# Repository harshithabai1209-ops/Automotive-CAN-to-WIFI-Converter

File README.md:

🚗 Automotive CAN-to-WiFi Converter(PCB DESIGN)
📌 Overview

This project implements an Automotive CAN (Controller Area Network) to Wi-Fi converter using a microcontroller with integrated Wi-Fi and a custom PCB designed in KiCad.
It allows vehicles’ CAN bus data (speed, RPM, fuel level, sensor data, etc.) to be captured, processed, and transmitted over Wi-Fi to mobile apps.

🚀 Features

Interfaces with standard Automotive CAN bus (OBD-II, ISO 11898)

Converts CAN frames into Wi-Fi packets

Supports protocols: MQTT, HTTP, WebSocket

Designed for low-latency data streaming

Custom KiCad PCB with CAN transceiver + Wi-Fi MCU

Optional SD card logging for offline analysis

Can be used for telematics, diagnostics, and fleet monitoring

🛠️ Hardware Components

Microcontroller (ESP32 / STM32 + ESP8266) → Wi-Fi + processing

CAN Transceiver (MCP2551 / SN65HVD230) → Interface between CAN bus & MCU

OBD-II Connector → Connection to vehicle CAN lines (CAN_H, CAN_L)

Power Supply

12V from car → Buck converter → 5V/3.3V regulated

Automotive-grade regulator (LM2596 / MP1584)

Protection Circuits

TVS Diodes for CAN line protection

Fuse & reverse polarity protection

Optional Modules

SD card (logging)

OLED/LCD (local display)

📐 PCB Design (KiCad)

Designed using KiCad EDA

2-layer PCB optimized for automotive use

Includes CAN transceiver + ESP32 footprint

Proper decoupling capacitors and EMI filters

Ground plane isolation between noisy CAN and Wi-Fi section

Connector footprint for OBD-II interface

Gerber files ready for fabrication

⚙️ Firmware / Software

Developed using Arduino IDE / ESP-IDF / STM32Cube

Features:

Reads CAN frames via CAN transceiver

Publishes data over Wi-Fi (MQTT/HTTP/WebSocket)

Supports real-time monitoring dashboard

Configurable baud rates (125 kbps, 250 kbps, 500 kbps)

🧩 Applications

Vehicle diagnostics (OBD-II data monitoring)

Fleet management & telematics

Real-time performance tracking (RPM, speed, fuel, etc.)

Research & development for automotive IoT

Data logging for predictive maintenance

⚠️ Safety Note

⚡ Caution: This project connects directly to the vehicle’s CAN bus. Incorrect wiring may damage ECU or other vehicle electronics. Ensure proper isolation and automotive-grade components are used.

📖 Future Enhancements

Support for Bluetooth + Wi-Fi dual mode

Cloud analytics with AI for predictive maintenance

Encryption for secure vehicle data transfer

Integration with mobile OBD-II diagnostic apps

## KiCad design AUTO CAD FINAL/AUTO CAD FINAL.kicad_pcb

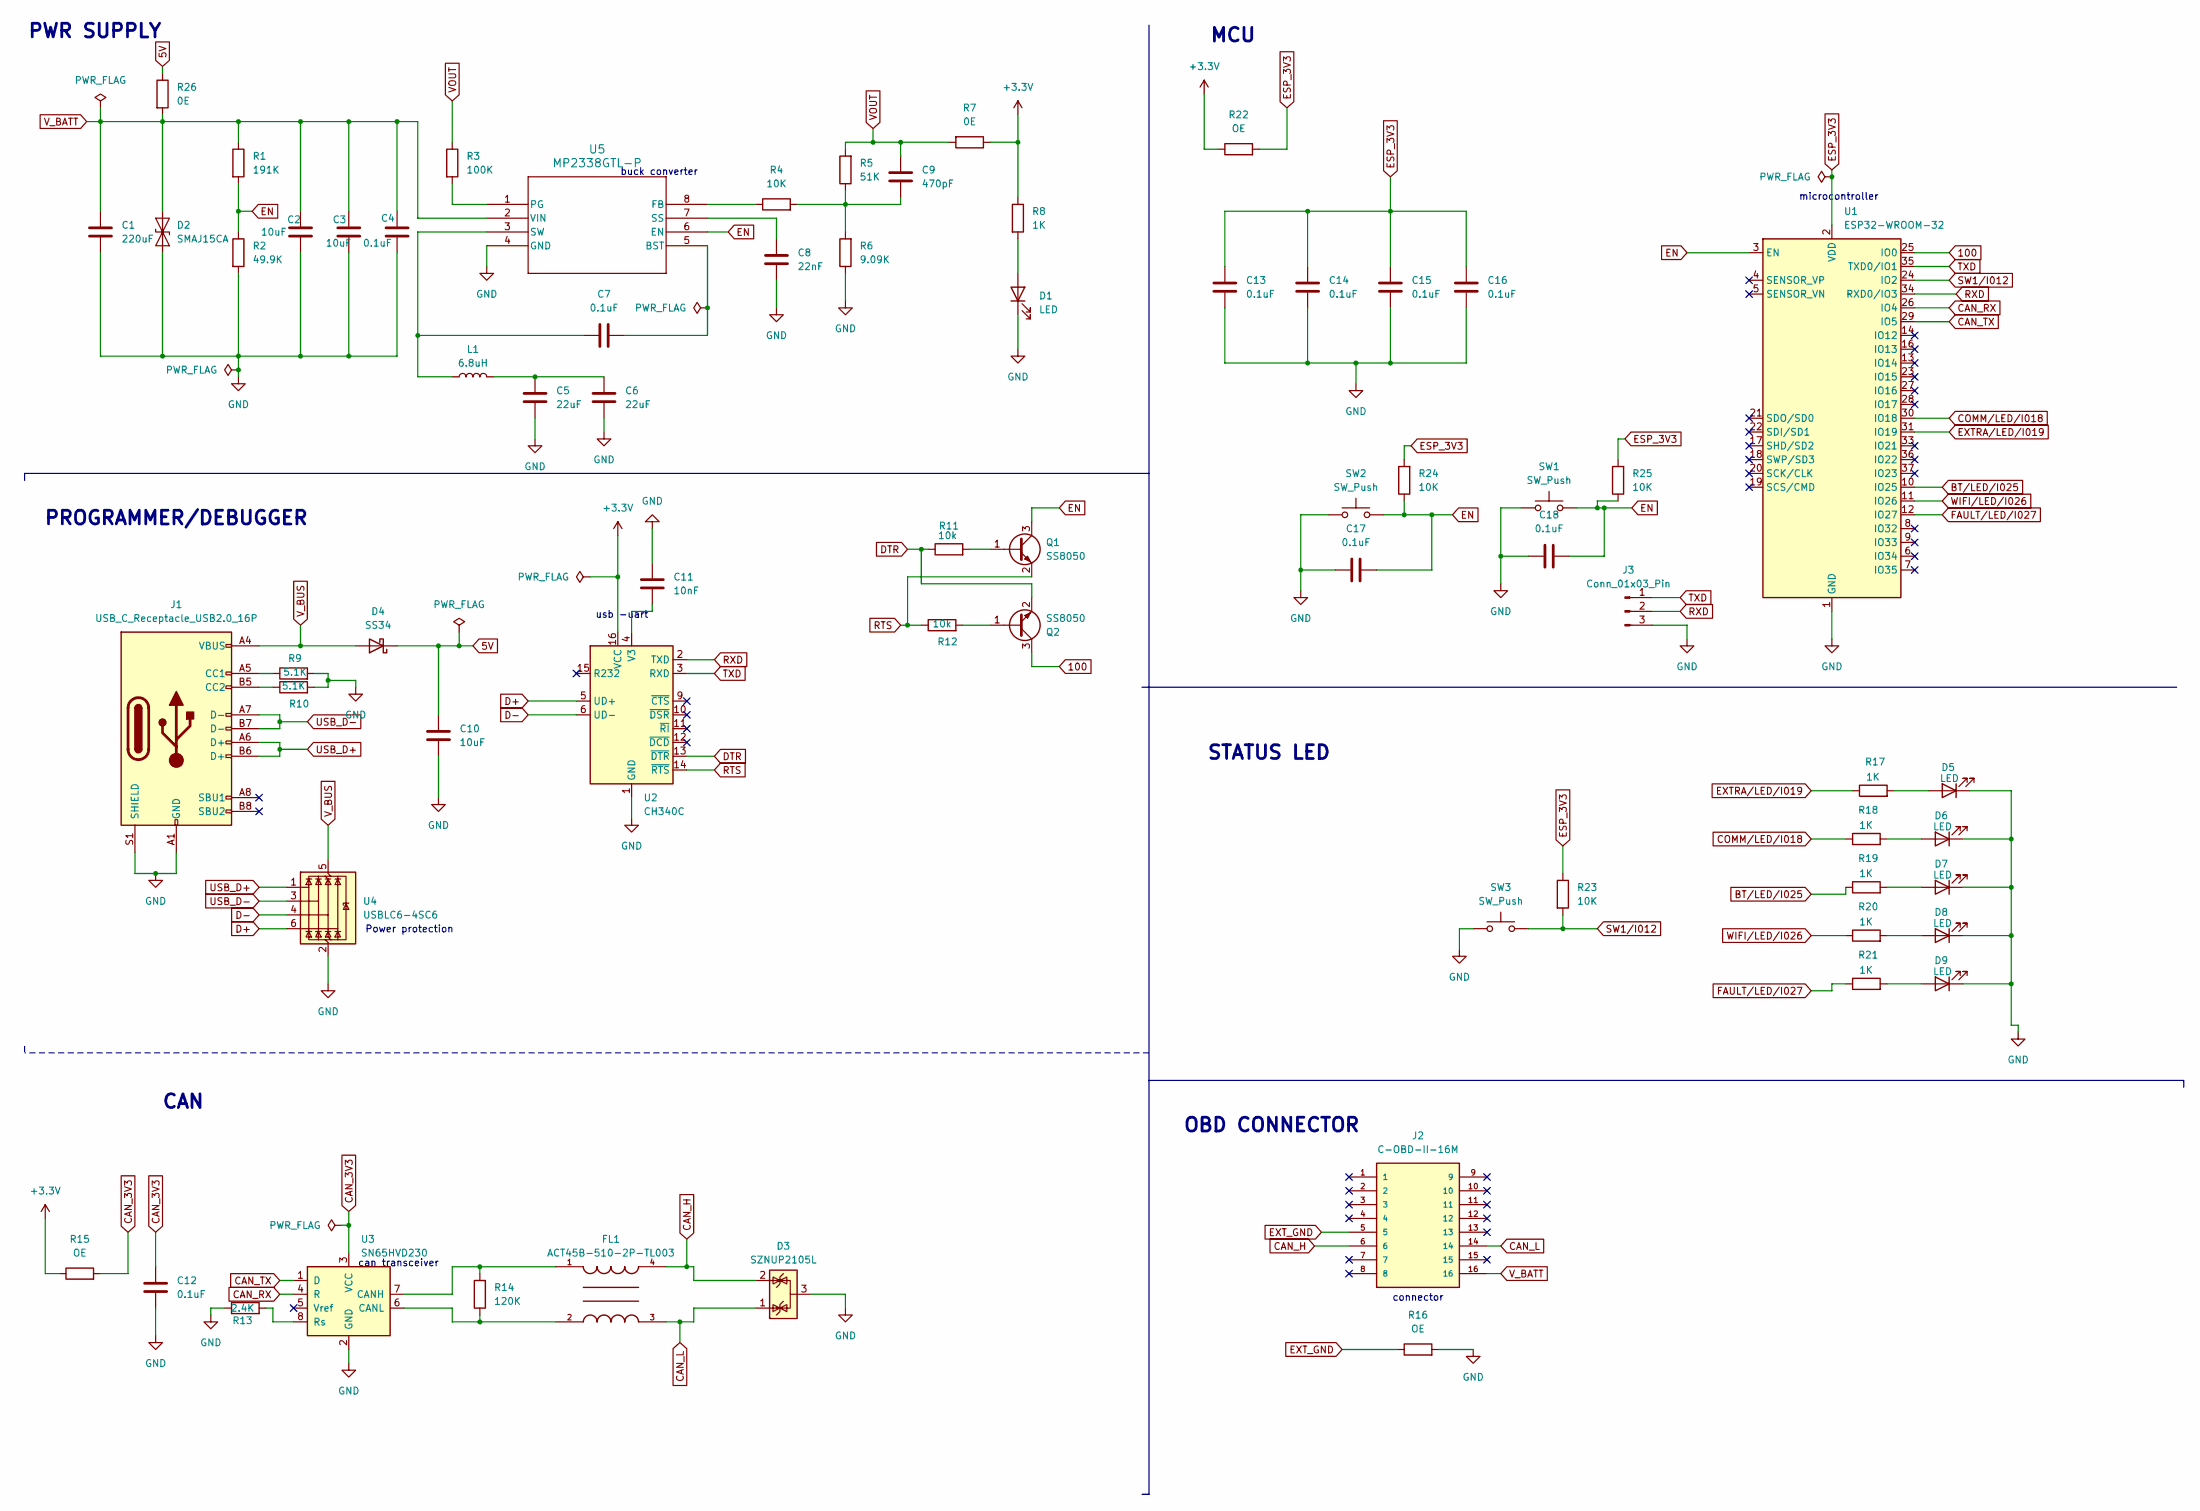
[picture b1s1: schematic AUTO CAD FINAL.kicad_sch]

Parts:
C1: 220uF; C_Elec_8x10.2
C2, C3, C10: 10uF; C_0603_1608Metric
C4, C7, C12, C13, C14, C15, C16, C17, C18: 0.1uF; C_0603_1608Metric
C5, C6: 22uF; C_1206_3216Metric
C8: 22nF; C_0603_1608Metric
C9: 470pF; C_0603_1608Metric
C11: 10nF; C_0603_1608Metric
D1, D5, D6, D7, D8, D9: LED; LED_0603_1608Metric
D2: SMAJ15CA; D_SMA
D3: SZNUP2105L; SOT-23
D4: SS34; D_SMA
FL1: ACT45B-510-2P-TL003; FIL_ACT45B-510-2P-TL003; PARTREV 20200405
J1: USB_C_Receptacle_USB2.0_16P; USB_C_Receptacle_HRO_TYPE-C-31-M-12
J2: C-OBD-II-16M; COMTECH_C-OBD-II-16M; PARTREV A
J3: Conn_01x03_Pin; PinHeader_1x03_P2.54mm_Vertical
L1: 6.8uH; L_6.3x6.3_H3
Q1, Q2: SS8050; SOT-23
R1: 191K; R_0603_1608Metric
R2: 49.9K; R_0603_1608Metric
R3: 100K; R_0603_1608Metric
R4, R23, R24, R25: 10K; R_0603_1608Metric
R5: 51K; R_0603_1608Metric
R6: 9.09K; R_0603_1608Metric
R7, R26: 0E; R_0603_1608Metric
R8, R17, R18, R19, R20, R21: 1K; R_0603_1608Metric
R9, R10: 5.1K; R_0603_1608Metric
R11, R12: 10k; R_0603_1608Metric
R13: 2.4K; R_0603_1608Metric
R14: 120K; R_0603_1608Metric
R15, R16, R22: OE; R_0603_1608Metric
SW1, SW2, SW3: SW_Push; SW_Push_SPST_NO_Alps_SKRK
U1: ESP32-WROOM-32
U2: CH340C; SOIC-16_3.9x9.9mm_P1.27mm
U3: SN65HVD230; SOIC-8_3.9x4.9mm_P1.27mm
U4: USBLC6-4SC6; SOT-23-6
U5: MP2338GTL-P; SOT-583-8

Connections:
5V: C10.2, D4.1 (K), R26.1
100: Q2.3 (C), U1.25 (IO0)
+3.3V: R7.1, R8.1, R15.1, R22.1, U2.16 (VCC)
BT/LED/I025: R19.1, U1.10 (IO25)
CAN_3V3: C12.2, R15.2, U3.3 (VCC)
CAN_H: D3.2 (K), FL1.4, J2.6
CAN_L: D3.1 (K), FL1.3, J2.14
CAN_RX: U1.26 (IO4), U3.4 (R)
CAN_TX: U1.29 (IO5), U3.1 (D)
COMM/LED/I018: R18.1, U1.30 (IO18)
D+: U2.5 (UD+), U4.6 (I/O4)
D-: U2.6 (UD-), U4.4 (I/O3)
DTR: Q2.2 (E), R11.1, U2.13 (~DTR)
EN: C17.1, C18.1, Q1.3 (C), R1.2, R2.1, R24.1, R25.1, SW1.2, SW2.2, U1.3 (EN), U5.6 (EN)
ESP_3V3: C13.2, C14.2, C15.2, C16.2, R22.2, R23.1, R24.2, R25.2, U1.2 (VDD)
EXTRA/LED/I019: R17.1, U1.31 (IO19)
EXT_GND: J2.5, R16.1
FAULT/LED/I027: R21.1, U1.12 (IO27)
GND: C1.2, C2.2, C3.2, C4.2, C5.2, C6.2, C8.1, C10.1, C11.2, C12.1, C13.1, C14.1, C15.1, C16.1, C17.2, C18.2, D1.1 (K), D2.1 (A1), D3.3 (A), D5.1 (K), D6.1 (K), D7.1 (K), D8.1 (K), D9.1 (K), J1.A1 (GND), J1.A12 (GND), J1.B1 (GND), J1.B12 (GND), J1.S1 (SHIELD), J3.3, R2.2, R6.1, R9.2, R10.2, R13.1, R16.2, SW1.1, SW2.1, SW3.1, U1.1 (GND), U1.15 (GND), U1.38 (GND), U1.39 (GND), U2.1 (GND), U3.2 (GND), U4.2 (GND), U5.4 (GND)
unnamed: C5.1, C6.1, L1.2
unnamed: C9.1, R4.2, R5.1, R6.2
unnamed: D1.2 (A), R8.2
unnamed: D5.2 (A), R17.2
unnamed: D6.2 (A), R18.2
unnamed: D7.2 (A), R19.2
unnamed: D8.2 (A), R20.2
unnamed: D9.2 (A), R21.2
unnamed: J1.A5 (CC1), R9.1
unnamed: J1.B5 (CC2), R10.1
unnamed: Q1.1 (B), R11.2
unnamed: Q2.1 (B), R12.2
unnamed: C11.1, U2.4 (V3)
unnamed: FL1.1, R14.2, U3.7 (CANH)
unnamed: FL1.2, R14.1, U3.6 (CANL)
unnamed: R13.2, U3.8 (Rs)
unnamed: C7.2, U5.5 (BST)
unnamed: R4.1, U5.8 (FB)
unnamed: R3.2, U5.1 (PG)
unnamed: C8.2, U5.7 (SS)
unnamed: C7.1, L1.1, U5.3 (SW)
RTS: Q1.2 (E), R12.1, U2.14 (~RTS)
RXD: J3.2, U1.34 (RXD0/IO3), U2.2 (TXD)
SW1/I012: R23.2, SW3.2, U1.24 (IO2)
TXD: J3.1, U1.35 (TXD0/IO1), U2.3 (RXD)
USB_D+: J1.A6 (D+), J1.B6 (D+), U4.1 (I/O1)
USB_D-: J1.A7 (D-), J1.B7 (D-), U4.3 (I/O2)
VOUT: C9.2, R3.1, R5.2, R7.2
V_BATT: C1.1, C2.1, C3.1, C4.1, D2.2 (A2), J2.16, R1.1, R26.2, U5.2 (VIN)
V_BUS: D4.2 (A), J1.A4 (VBUS), J1.A9 (VBUS), J1.B4 (VBUS), J1.B9 (VBUS), U4.5 (VBUS)
WIFI/LED/I026: R20.1, U1.11 (IO26)

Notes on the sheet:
MCU
usb -uart
connector
can transceiver
microcontroller
OBD CONNECTOR
CAN
PWR SUPPLY
buck converter
Power protection
PROGRAMMER/DEBUGGER
STATUS LED

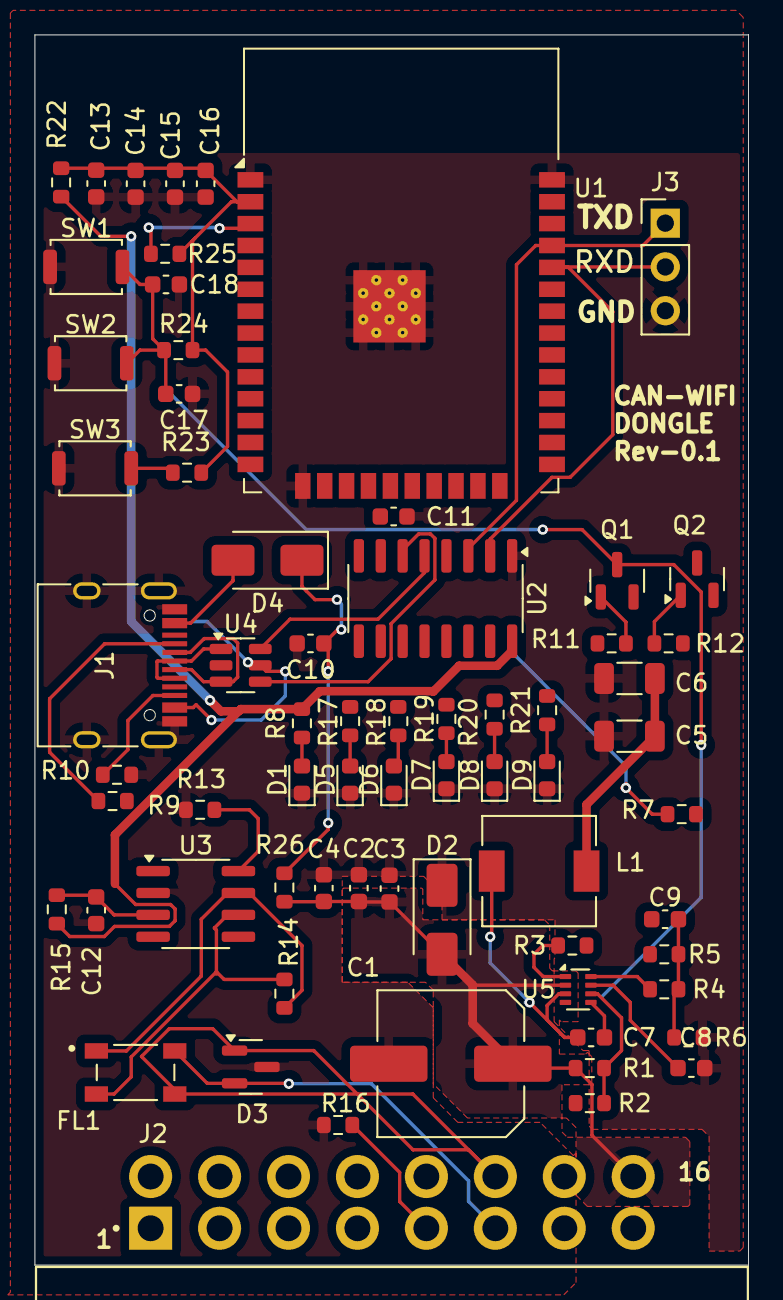
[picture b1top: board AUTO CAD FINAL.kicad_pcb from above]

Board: 2 copper layers, 41.4 x 71.4 mm, 68 parts (0 on the bottom side), 50 nets.

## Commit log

2025-08-15 Add files via upload
    initial commit
